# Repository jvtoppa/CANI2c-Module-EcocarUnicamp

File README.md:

# Eco-CAN V1.1

A simple modular PCB for CAN, I2c and headlights connectors. This controller was designed in order to simplify the electrical systems that partake in our Urban Vehicle.

By integrating CAN and I2C communication protocols, this board enables seamless interaction between various electronic modules while reducing wiring complexity. The dedicated headlight connectors allow for easy control of lighting systems.

## Features:

Modular Design – Allows for easy expansion and integration with CAN systems;

CAN Bus Support – Enables reliable communication with automotive-grade peripherals;

I2C Interface – Facilitates low-power communication with multiple sensors while also integrating with our telemmetry system in the CAN Network;

Headlight Control – Simplifies wiring and management of lighting components;

## Feedback

If you have any feedback/questions regarding this PCB, contact us at our [website](https://sites.google.com/dac.unicamp.br/ecocarunicamp/ "website").

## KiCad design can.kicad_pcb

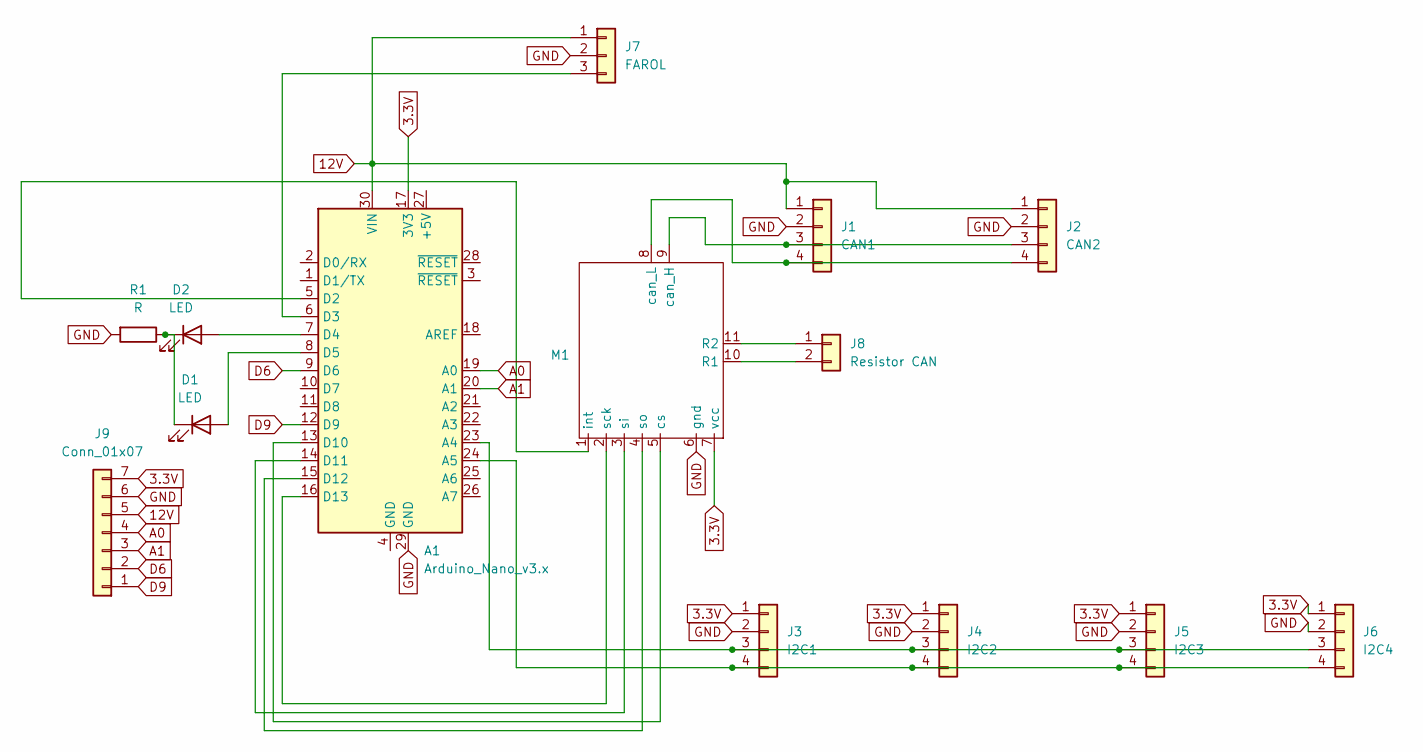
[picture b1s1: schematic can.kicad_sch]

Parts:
A1: Arduino_Nano_v3.x; Arduino_Nano
D1, D2: LED; LED_D5.0mm
J1: CAN1; JST_XH_B4B-XH-A_1x04_P2.50mm_Vertical
J2: CAN2; JST_XH_B4B-XH-A_1x04_P2.50mm_Vertical
J3: I2C1; JST_XH_B4B-XH-A_1x04_P2.50mm_Vertical
J4: I2C2; JST_XH_B4B-XH-A_1x04_P2.50mm_Vertical
J5: I2C3; JST_XH_B4B-XH-A_1x04_P2.50mm_Vertical
J6: I2C4; JST_XH_B4B-XH-A_1x04_P2.50mm_Vertical
J7: FAROL; JST_XH_B3B-XH-A_1x03_P2.50mm_Vertical
J8: Resistor CAN; PinHeader_2x01_P2.00mm_Vertical
J9: Conn_01x07; PinHeader_1x07_P2.54mm_Vertical
M1: MCP2515
R1: R; R_Axial_DIN0204_L3.6mm_D1.6mm_P7.62mm_Horizontal

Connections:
3.3V: A1.17 (3V3), J3.1, J4.1, J5.1, J6.1, J9.7, M1.7 (vcc)
12V: A1.30 (VIN), J1.1, J2.1, J7.1, J9.5; also elsewhere on the board
A0: A1.19 (A0), J9.4
A1: A1.20 (A1), J9.3
D6: A1.9 (D6), J9.2
D9: A1.12 (D9), J9.1
GND: A1.29 (GND), J1.2, J2.2, J3.2, J4.2, J5.2, J6.2, J7.2, J9.6, M1.6 (gnd), R1.2; also elsewhere on the board
unnamed: A1.23 (A4), J3.3, J4.3, J5.3, J6.3
unnamed: A1.24 (A5), J3.4, J4.4, J5.4, J6.4
unnamed: A1.5 (D2), M1.1 (int)
unnamed 10: A1.6 (D3), J7.3; also elsewhere on the board
unnamed: A1.7 (D4), D2.2 (A)
unnamed: A1.8 (D5), D1.2 (A)
unnamed: A1.13 (D10), M1.5 (cs)
unnamed: A1.14 (D11), M1.3 (si)
unnamed: A1.15 (D12), M1.4 (so)
unnamed: A1.16 (D13), M1.2 (sck)
unnamed: D1.1 (K), D2.1 (K), R1.1
unnamed: J1.3, J2.3, M1.9 (can_H)
unnamed: J1.4, J2.4, M1.8 (can_L)
unnamed: J8.1, M1.11 (R2)
unnamed: J8.2, M1.10 (R1)

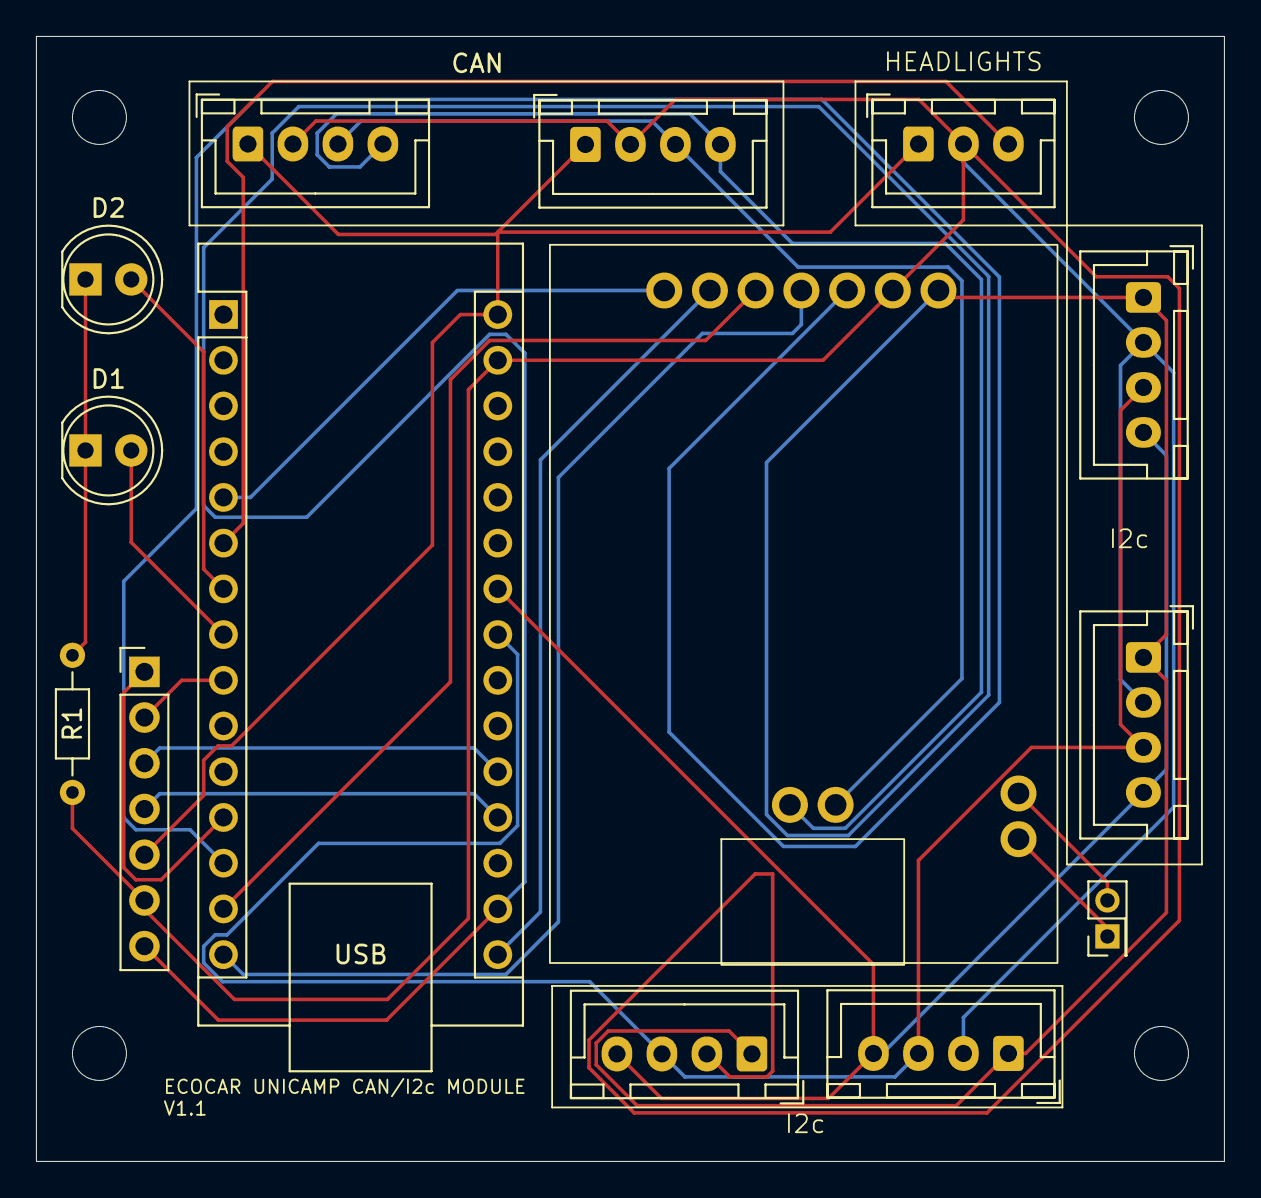
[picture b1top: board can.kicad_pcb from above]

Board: 2 copper layers, 66.0 x 62.5 mm, 14 parts (0 on the bottom side), 22 nets.

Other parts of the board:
CAN: FAROL; JST_XH_B3B-XH-A_1x03_P2.50mm_Vertical

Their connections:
12V: CAN.1; also elsewhere on the board
GND: CAN.2; also elsewhere on the board
unnamed 10: CAN.3; also elsewhere on the board
